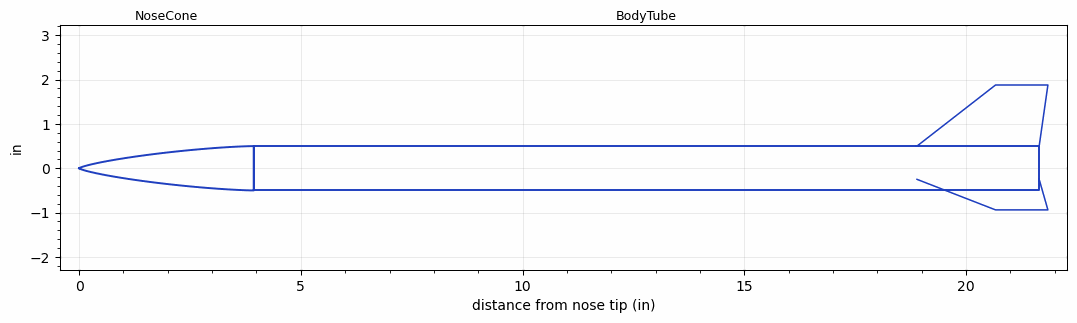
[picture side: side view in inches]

<RASAeroDocument>
 <FileVersion>2</FileVersion>
 <RocketDesign>
  <NoseCone>
   <Length>3.9370079</Length>
   <Diameter>1</Diameter>
   <Shape>Von Karman Ogive</Shape>
   <Location>0</Location>
  </NoseCone>
  <BodyTube>
   <Length>17.716535</Length>
   <Diameter>1</Diameter>
   <RailGuideDiameter>0.31496063</RailGuideDiameter>
   <RailGuideHeight>0.31496063</RailGuideHeight>
   <Location>3.9370079</Location>
   <Fin>
    <Count>3</Count>
    <Chord>2.7559055</Chord>
    <Span>1.3779528</Span>
    <SweepDistance>1.7716535</SweepDistance>
    <TipChord>1.1811024</TipChord>
    <Thickness>0.078740157</Thickness>
    <Location>2.7559055</Location>
    <AirfoilSection>Square</AirfoilSection>
   </Fin>
  </BodyTube>
  <Surface>Rough Camouflage Paint</Surface>
  <ModifiedBarrowman>False</ModifiedBarrowman>
  <Turbulence>False</Turbulence>
  <UseBooster1>False</UseBooster1>
  <UseBooster2>False</UseBooster2>
  <Comments>Exported by lo-fi-rocket from "r3-minimum-diameter-24".</Comments>
 </RocketDesign>
 <LaunchSite>
  <Altitude>0</Altitude>
  <Pressure>0</Pressure>
  <RodAngle>0</RodAngle>
  <RodLength>4.9212598</RodLength>
  <Temperature>59</Temperature>
  <WindSpeed>0</WindSpeed>
 </LaunchSite>
 <Recovery>
  <Altitude1>1000</Altitude1>
  <Altitude2>1000</Altitude2>
  <DeviceType1>Parachute</DeviceType1>
  <DeviceType2>None</DeviceType2>
  <Event1>True</Event1>
  <Event2>False</Event2>
  <Size1>11.811024</Size1>
  <Size2>0</Size2>
  <EventType1>Apogee</EventType1>
  <EventType2>None</EventType2>
  <CD1>0.8</CD1>
  <CD2>1.33</CD2>
 </Recovery>
 <SimulationList>
  <Simulation>
   <SustainerEngine>LF-F39T  (LoFi)</SustainerEngine>
   <SustainerLaunchWt>0.37891711</SustainerLaunchWt>
   <SustainerCG>14.025488</SustainerCG>
   <SustainerIgnitionDelay>0</SustainerIgnitionDelay>
   <Booster1SeparationDelay>0</Booster1SeparationDelay>
   <Booster1IgnitionDelay>0</Booster1IgnitionDelay>
   <IncludeBooster1>False</IncludeBooster1>
   <Booster2Delay>0</Booster2Delay>
   <IncludeBooster2>False</IncludeBooster2>
  </Simulation>
 </SimulationList>
</RASAeroDocument>
